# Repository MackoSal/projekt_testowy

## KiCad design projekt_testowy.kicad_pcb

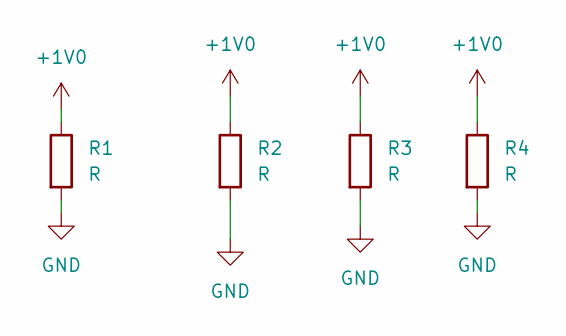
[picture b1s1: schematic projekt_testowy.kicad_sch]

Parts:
R1, R2, R3, R4: R; R_Axial_DIN0207_L6.3mm_D2.5mm_P10.16mm_Horizontal

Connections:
+1V0: R1.1, R2.1, R3.1, R4.1
GND: R1.2, R2.2, R3.2, R4.2

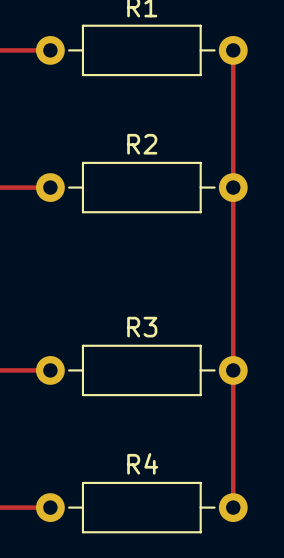
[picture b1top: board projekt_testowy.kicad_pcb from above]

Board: 2 copper layers, 4 parts (0 on the bottom side), 2 nets.

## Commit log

2022-03-01 dodanie drugiej lini
    a to komentarz
2022-03-01 dodanie 3 linii
    koment
2022-03-01 dodanie 4 linii
    comment
2022-03-01 dodanie rezystorow na shemacie
    4 rezystory tht
2022-03-01 rozlozenie 4 rezystorow
    celowo zle (kwadratowe) polaczenia
2022-03-01 dodanie krzywych polaczen
    beda wymagac poprawy
2022-03-01 poprawa polaczen
    polaczenia w linii
